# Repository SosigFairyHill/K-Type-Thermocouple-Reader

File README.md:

Thermocouple voltages read in using a senstivie high-precision ADC. Junction temperature measured using a temperature sensor. Control using a PIC16F886 and temperatures output onto a pair of 7-segment LED displays.

Circuit board and schematic created in Eagle. Software written in MPLabX.

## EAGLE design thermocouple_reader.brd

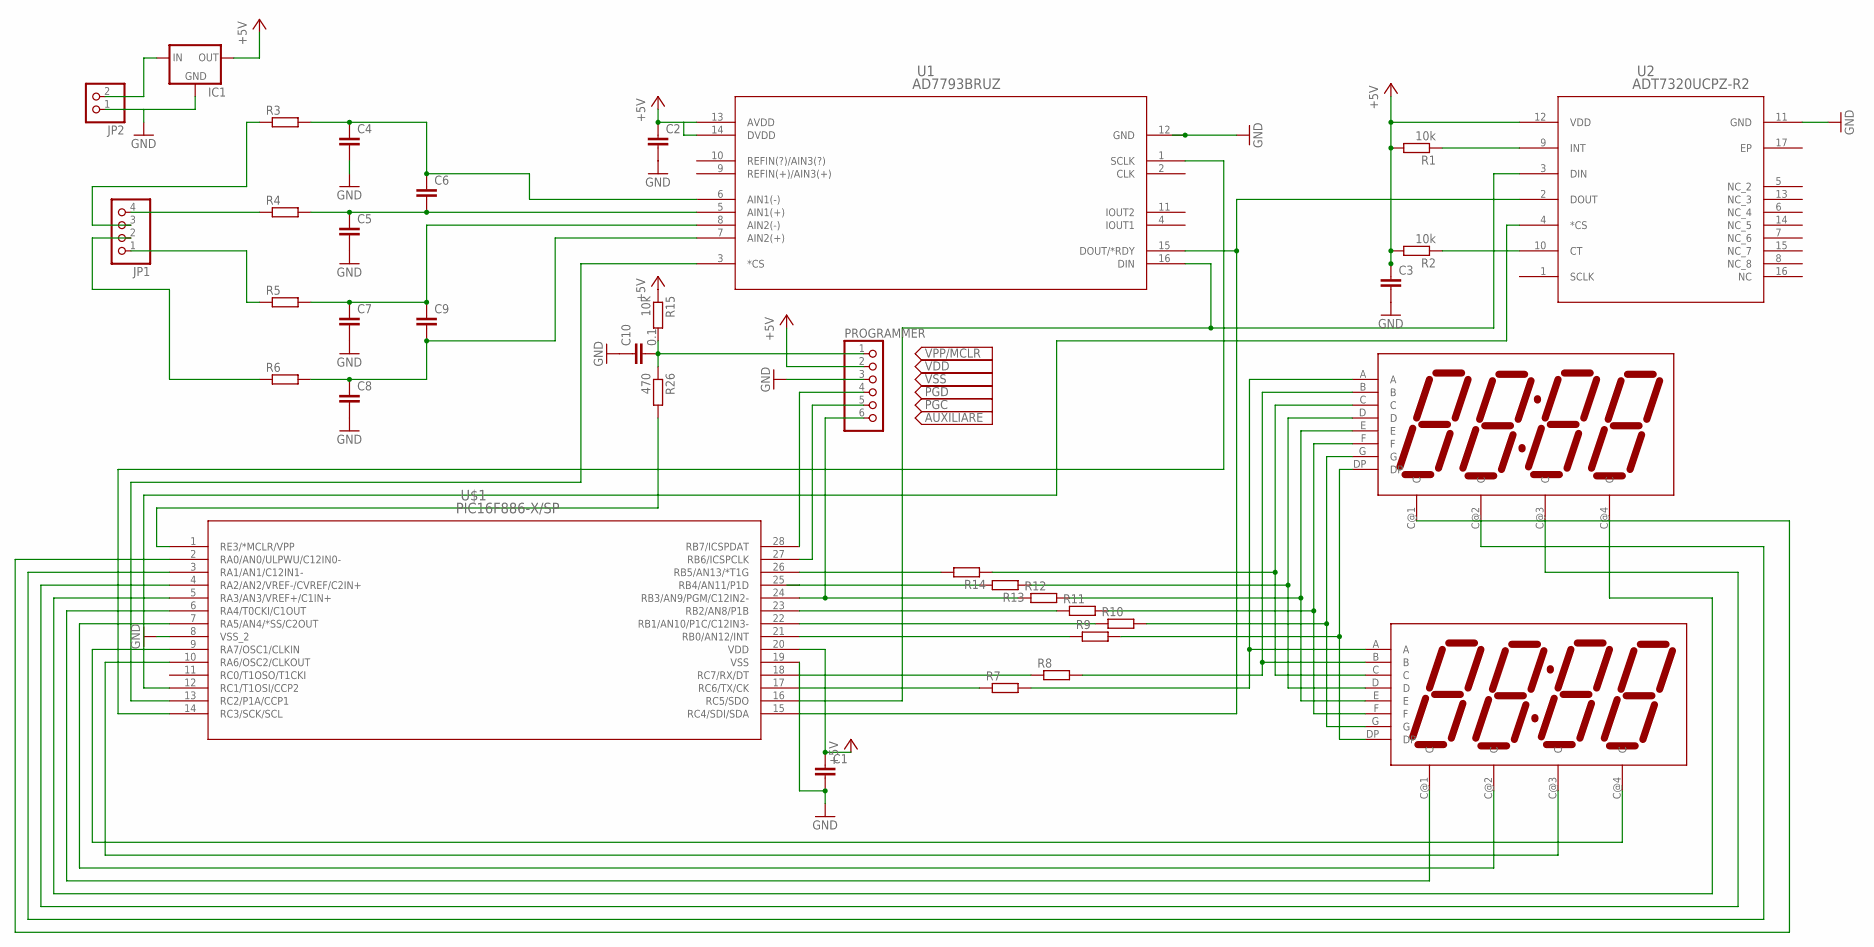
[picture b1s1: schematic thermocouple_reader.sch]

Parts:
C1, C2, C3, C6, C9: C-EU025-024X044; C025-024X044
C4, C5, C7, C8: C-EU025-025X050; C025-025X050
C10: 0.1; C025-025X050
IC1: 78LXX
JP1: PINHD-1X4; 1X04
JP2: PINHD-1X2; 1X02
PROGRAMMER: PINHD-1X6; 1X06
R1, R2, R15: 10k; 0204/5
R3, R4, R5, R6, R12, R13: R-EU_0204/5; 0204/5
R7: R-EU_0207/10; 0207/10
R8, R9, R10, R11, R14: R-EU_0207/15; 0207/15
R26: 470; 0204/5
U1: AD7793BRUZ; RU_16
U2: ADT7320UCPZ-R2; CP_16_17
U$1: PIC16F886-X/SP; SPDIP28_300MC
U$2, U$3: HDSP-BO1E; HDSP-B01

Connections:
+5V: C1.1, C2.1, C3.1, IC1.OUT, PROGRAMMER.2, R1.2, R2.2, R15.1, U1.13 (AVDD), U1.14 (DVDD), U2.12 (VDD), U$1.20 (VDD)
AUXILIARE: PROGRAMMER.6, R12.1, U$1.24 (RB3/AN9/PGM/C12IN2-)
GND: C1.2, C2.2, C3.2, C4.2, C5.2, C7.2, C8.2, C10.1, IC1.GND, JP2.1, PROGRAMMER.3, U1.12 (GND), U2.11 (GND), U$1.8 (VSS_2), U$1.19 (VSS)
unnamed: C4.1, C6.1, R3.2, U1.6 (AIN1(-))
unnamed: U1.16 (DIN), U2.3 (DIN), U$1.16 (RC5/SDO)
unnamed: U1.1 (SCLK), U$1.14 (RC3/SCK/SCL)
unnamed: U1.3 (*CS), U$1.13 (RC2/P1A/CCP1)
unnamed: U2.4 (*CS), U$1.12 (RC1/T1OSI/CCP2)
unnamed: U1.15 (DOUT/*RDY), U2.2 (DOUT), U$1.15 (RC4/SDI/SDA)
unnamed: C5.1, C6.2, R4.2, U1.5 (AIN1(+))
unnamed: C7.1, C9.1, R5.2, U1.8 (AIN2(-))
unnamed: R1.1, U2.9 (INT)
unnamed: R2.1, U2.10 (CT)
unnamed: C8.1, C9.2, R6.2, U1.7 (AIN2(+))
unnamed: R10.2, U$2.G, U$3.G
unnamed: R9.2, U$2.DP, U$3.DP
unnamed: R11.2, U$2.F, U$3.F
unnamed: R12.2, U$2.E, U$3.E
unnamed: R13.1, U$2.D, U$3.D
unnamed: R14.1, U$2.C, U$3.C
unnamed: R8.2, U$2.B, U$3.B
unnamed: R7.2, U$2.A, U$3.A
unnamed: R14.2, U$1.26 (RB5/AN13/*T1G)
unnamed: R13.2, U$1.25 (RB4/AN11/P1D)
unnamed: C10.2, PROGRAMMER.1, R15.2, R26.1
unnamed: R11.1, U$1.23 (RB2/AN8/P1B)
unnamed: R10.1, U$1.22 (RB1/AN10/P1C/C12IN3-)
unnamed: R9.1, U$1.21 (RB0/AN12/INT)
unnamed: R8.1, U$1.18 (RC7/RX/DT)
unnamed: R7.1, U$1.17 (RC6/TX/CK)
unnamed: U$1.9 (RA7/OSC1/CLKIN), U$3.C@4 (C)
unnamed: U$1.10 (RA6/OSC2/CLKOUT), U$3.C@3 (C)
unnamed: U$1.7 (RA5/AN4/*SS/C2OUT), U$3.C@2 (C)
unnamed: U$1.6 (RA4/T0CKI/C1OUT), U$3.C@1 (C)
unnamed: U$1.5 (RA3/AN3/VREF+/C1IN+), U$2.C@4 (C)
unnamed: U$1.4 (RA2/AN2/VREF-/CVREF/C2IN+), U$2.C@3 (C)
unnamed: U$1.3 (RA1/AN1/C12IN1-), U$2.C@2 (C)
unnamed: U$1.2 (RA0/AN0/ULPWU/C12IN0-), U$2.C@1 (C)
unnamed: JP1.3, R3.1
unnamed: JP1.4, R4.1
unnamed: JP1.1, R5.1
unnamed: JP1.2, R6.1
unnamed: IC1.IN, JP2.2
PGC: PROGRAMMER.5, U$1.27 (RB6/ICSPCLK)
PGD: PROGRAMMER.4, U$1.28 (RB7/ICSPDAT)
VPP/MCLR: R26.2, U$1.1 (RE3/*MCLR/VPP)

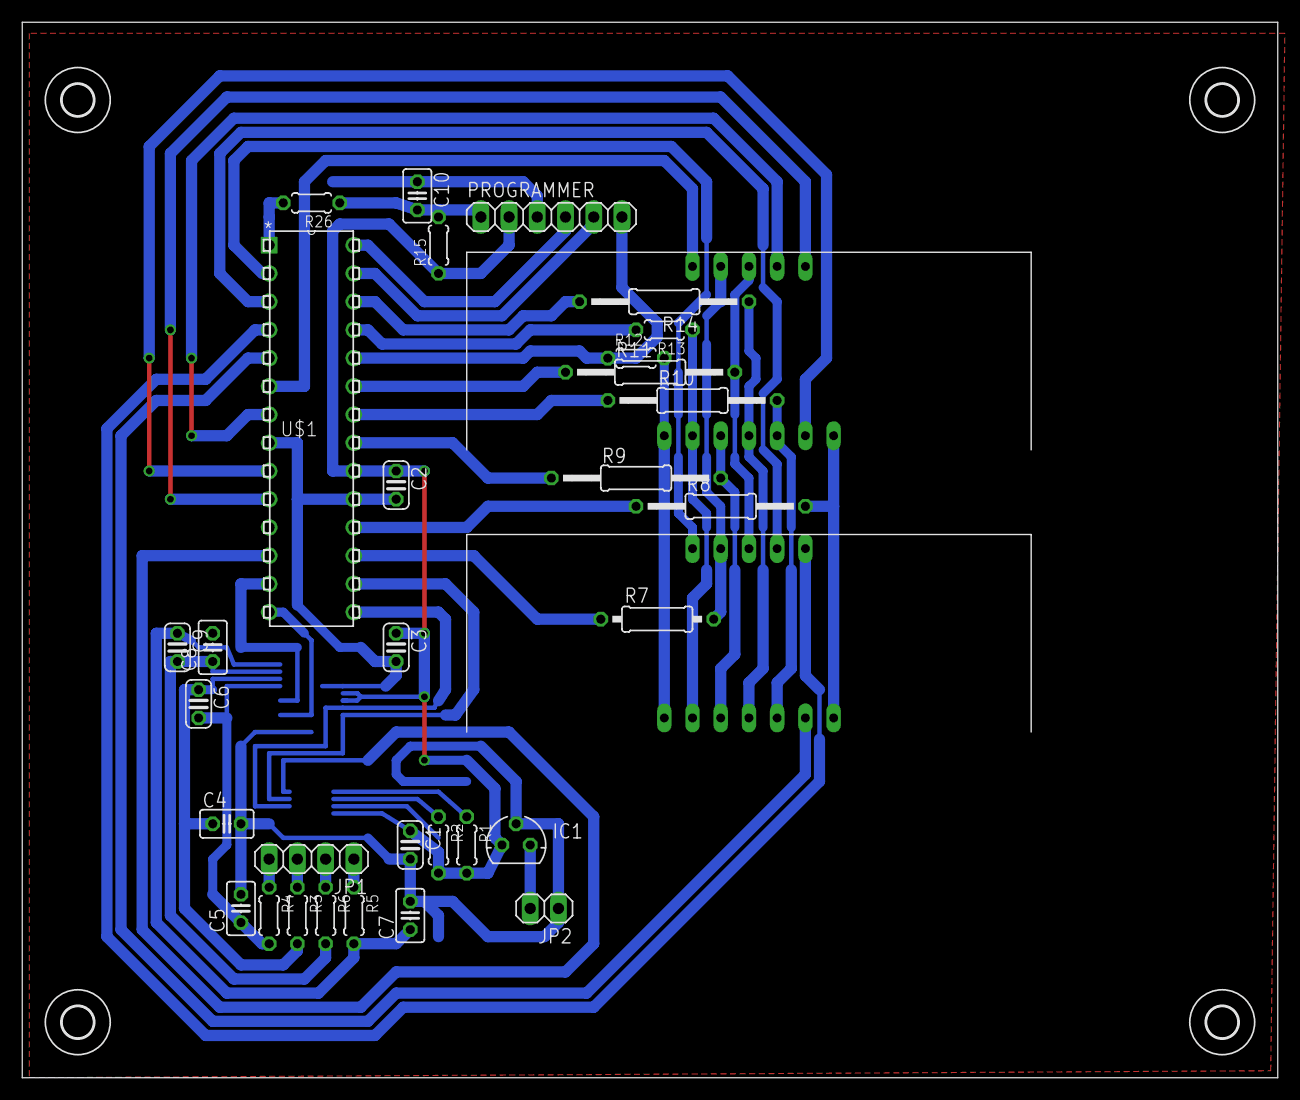
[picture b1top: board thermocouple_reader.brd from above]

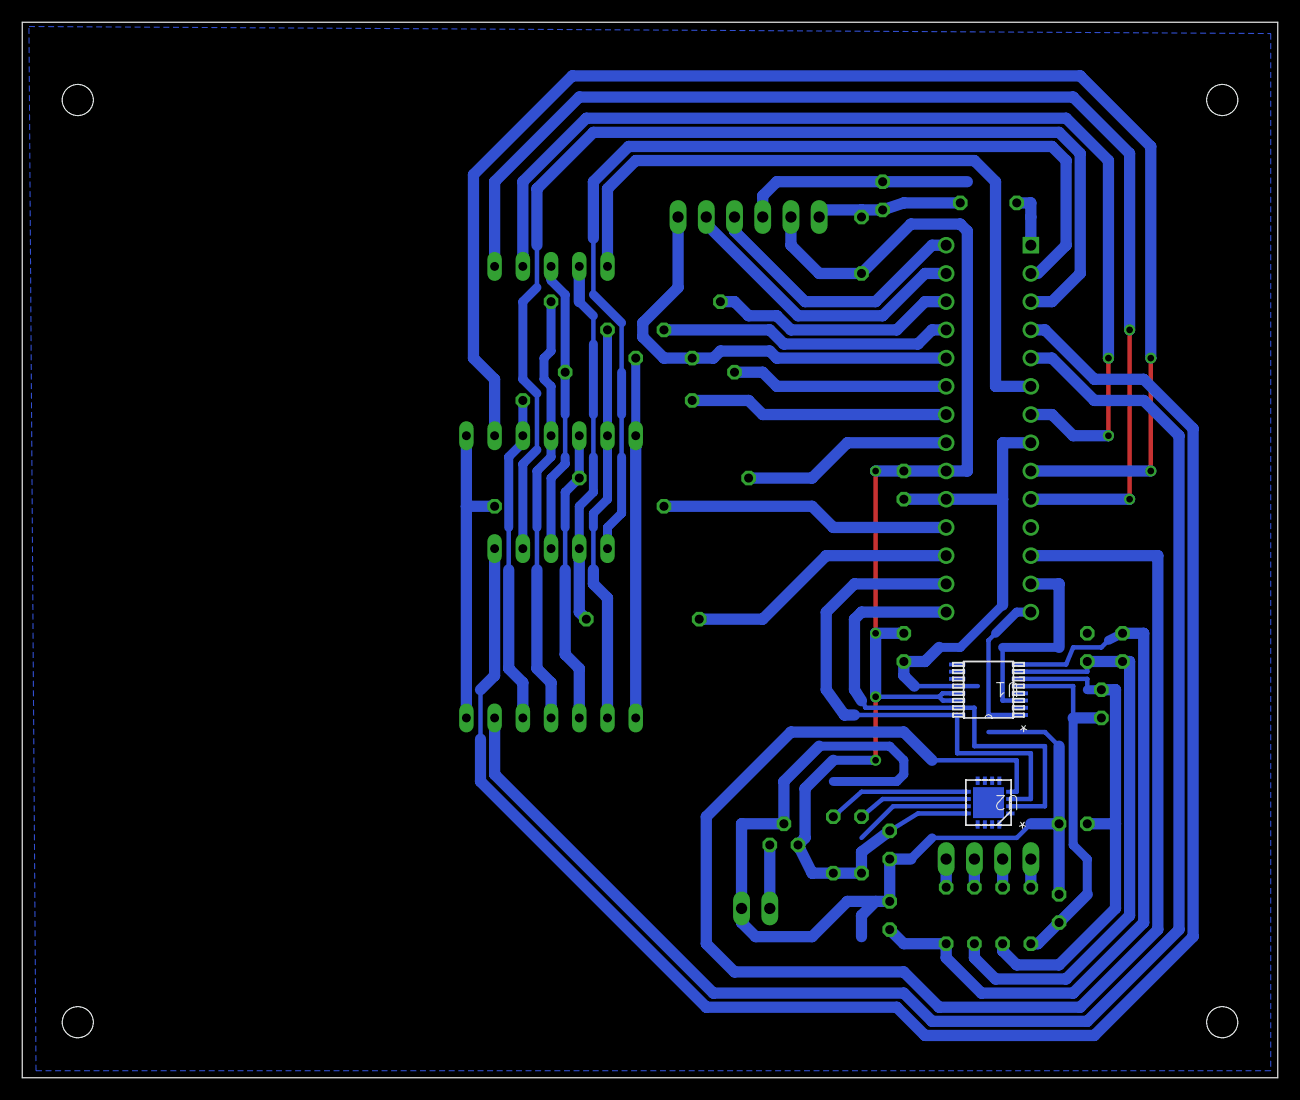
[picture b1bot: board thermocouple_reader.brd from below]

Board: 2 copper layers, 113.0 x 95.0 mm, 39 parts (2 on the bottom side), 46 nets.

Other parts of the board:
U$4, U$5, U$6, U$7: 2,8

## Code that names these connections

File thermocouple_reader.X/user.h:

/******************************************************************************/
/* User Level #define Macros                                                  */
/******************************************************************************/
#define SEGMENT_A PORTCbits.RC6
#define SEGMENT_B PORTCbits.RC7
#define SEGMENT_C PORTBbits.RB5
#define SEGMENT_D PORTBbits.RB4
#define SEGMENT_E PORTBbits.RB3
#define SEGMENT_F PORTBbits.RB2
#define SEGMENT_G PORTBbits.RB1
#define SEGMENT_DP PORTBbits.RB0
/* TODO Application specific user parameters used in user.c may go here */

/******************************************************************************/
/* User Function Prototypes                                                   */
/******************************************************************************/

/* TODO User level functions prototypes (i.e. InitApp) go here */

void InitApp(void);         /* I/O and Peripheral Initialization */

char* display_number(float);

void select_chip(int);

void buf_wait();

void seven_segment(float, int);

int binary_decimal(int n);

float temp_voltage(float);

float voltage_temp(float);

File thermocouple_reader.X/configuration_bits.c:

/******************************************************************************/
/* Main Files to Include                                                      */
/******************************************************************************/

#if defined(__XC)
    #include <xc.h>         /* XC8 General Include File */
#elif defined(HI_TECH_C)
    #include <htc.h>        /* HiTech General Include File */
#endif

/******************************************************************************/
/* Configuration Bits                                                         */
/*                                                                            */
/* Refer to your Hi-Tech User Manual in the PICC installation directory       */
/* /doc folder for more information on filling in configuration bits.         */
/* In addition, configuration bit mnemonics can be found in your              */
/* PICC\version\include\<processor name>.h file for your device.  The XC8     */
/* compiler contains documentation on the configuration bit macros within     */
/* the compiler installation /docs folder in a file called                    */
/* pic18_chipinfo.html.                                                       */
/*                                                                            */
/* For additional information about what the hardware configurations mean in  */
/* terms of device operation, refer to the device datasheet.                  */
/*                                                                            */
/* A feature of MPLAB X is the 'Generate Source Code to Output' utility in    */
/* the Configuration Bits window.  Under Window > PIC Memory Views >          */
/* Configuration Bits, a user controllable configuration bits window is       */
/* available to Generate Configuration Bits source code which the user can    */
/* paste into this project.                                                   */
/*                                                                            */
/******************************************************************************/

/* TODO Fill in your config bits here.  Use the configuration bits generator/ */
// CONFIG1
#pragma config FOSC = INTRC_NOCLKOUT// Oscillator Selection bits (INTOSCIO oscillator: I/O function on RA6/OSC2/CLKOUT pin, I/O function on RA7/OSC1/CLKIN)
#pragma config WDTE = ON        // Watchdog Timer Enable bit (WDT enabled)
#pragma config PWRTE = ON       // Power-up Timer Enable bit (PWRT enabled)
#pragma config MCLRE = OFF      // RE3/MCLR pin function select bit (RE3/MCLR pin function is digital input, MCLR internally tied to VDD)
#pragma config CP = OFF         // Code Protection bit (Program memory code protection is disabled)
#pragma config CPD = OFF        // Data Code Protection bit (Data memory code protection is disabled)
#pragma config BOREN = ON       // Brown Out Reset Selection bits (BOR enabled)
#pragma config IESO = ON        // Internal External Switchover bit (Internal/External Switchover mode is enabled)
#pragma config FCMEN = ON       // Fail-Safe Clock Monitor Enabled bit (Fail-Safe Clock Monitor is enabled)
#pragma config LVP = ON         // Low Voltage Programming Enable bit (RB3/PGM pin has PGM function, low voltage programming enabled)

// CONFIG2
#pragma config BOR4V = BOR21V   // Brown-out Reset Selection bit (Brown-out Reset set to 2.1V)
#pragma config WRT = OFF        // Flash Program Memory Self Write Enable bits (Write protection off)
